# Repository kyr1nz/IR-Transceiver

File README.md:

# IR-Transceiver
ESP32-based infrared transceiver for receiving, decoding, and transmitting IR signals.

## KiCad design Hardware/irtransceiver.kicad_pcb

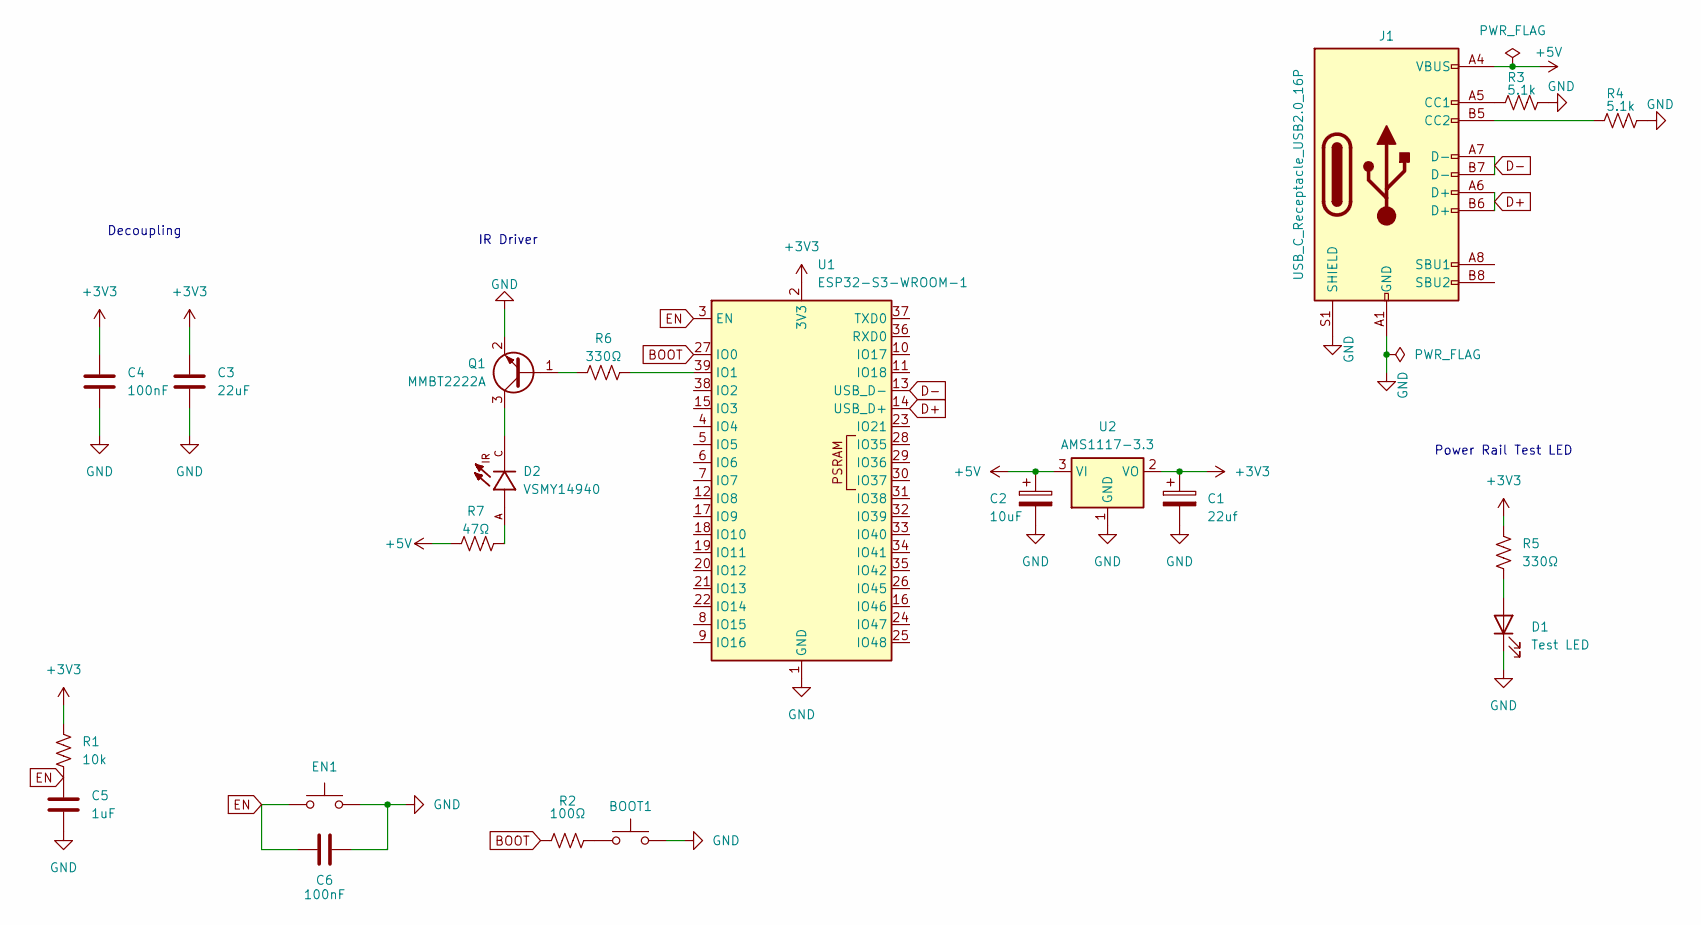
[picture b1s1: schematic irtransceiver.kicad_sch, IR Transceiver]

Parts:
BOOT1: BOOT Switch; SW-SMD_L3.9-W3.0-P4.45; LCSC C720477
C1: 22uf; C_1210_3225Metric; LCSC C696813
C2: 10uF; C_1210_3225Metric; LCSC C7194
C3: 22uF; C_0805_2012Metric; LCSC C602037
C4, C6: 100nF; C_0805_2012Metric; LCSC C83055
C5: 1uF; C_0805_2012Metric; LCSC C28323
D1: Test LED; LED_0603_1608Metric; LCSC C126319
D2: VSMY14940; LED_MY14940_VIS; PARTREV 1.6; LCSC C511069
EN1: EN Switch; SW-SMD_L3.9-W3.0-P4.45; LCSC C720477
J1: USB_C_Receptacle_USB2.0_16P; USB_C_Receptacle_GCT_USB4105-xx-A_16P_TopMnt_Horizontal; LCSC C393939
Q1: MMBT2222A; SOT-23; LCSC C179396
R1: 10k; R_0805_2012Metric; LCSC C2907219
R2: 100Ω; R_0805_2012Metric; LCSC C105577
R3, R4: 5.1k; R_0805_2012Metric; LCSC C27834
R5: 330Ω; R_0805_2012Metric; LCSC C17630
R6: 330Ω; R_0603_1608Metric; LCSC C105879
R7: 47Ω; R_2512_6332Metric; LCSC C175524
U1: ESP32-S3-WROOM-1; LCSC C2913202
U2: AMS1117-3.3; SOT-223-3_TabPin2; LCSC C6186

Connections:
+3V3: C1.1, C3.1, C4.1, R1.1, R5.1, U1.2 (3V3), U2.2 (VO)
+5V: C2.1, J1.A4 (VBUS), J1.A9 (VBUS), J1.B4 (VBUS), J1.B9 (VBUS), R7.1, U2.3 (VI)
BOOT: R2.1, U1.27 (IO0)
D+: J1.A6 (D+), J1.B6 (D+), U1.14 (USB_D+)
D-: J1.A7 (D-), J1.B7 (D-), U1.13 (USB_D-)
EN: C5.1, C6.1, EN1.1, R1.2, U1.3 (EN)
GND: BOOT1.2, C1.2, C2.2, C3.2, C4.2, C5.2, C6.2, D1.1 (K), EN1.2, J1.A1 (GND), J1.A12 (GND), J1.B1 (GND), J1.B12 (GND), J1.S1 (SHIELD), Q1.2 (E), R3.2, R4.2, U1.1 (GND), U1.40 (GND), U1.41 (GND), U2.1 (GND)
unnamed: BOOT1.1, R2.2
unnamed: D1.2 (A), R5.2
unnamed: D2.A, R7.2
unnamed: J1.A5 (CC1), R3.1
unnamed: J1.B5 (CC2), R4.1
unnamed: Q1.1 (B), R6.1
unnamed: D2.C, Q1.3 (C)
unnamed: R6.2, U1.39 (IO1)

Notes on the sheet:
Decoupling
Power Rail Test LED
IR Driver

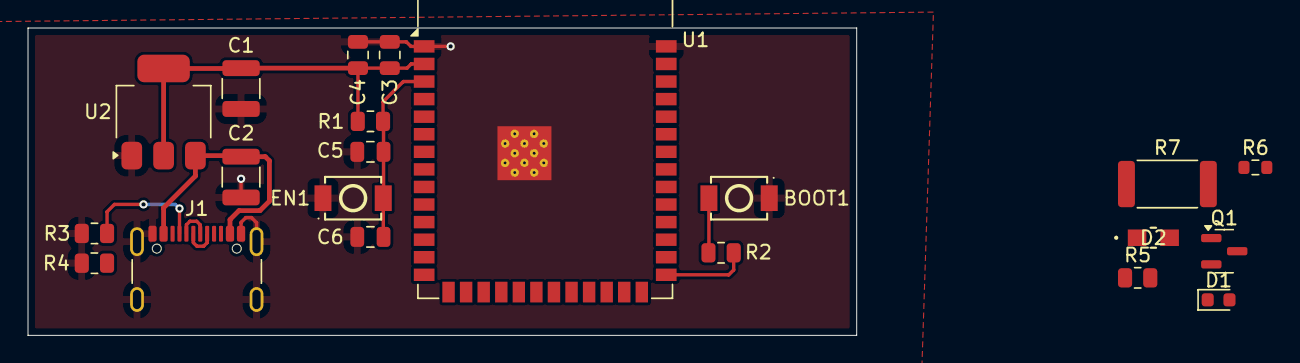
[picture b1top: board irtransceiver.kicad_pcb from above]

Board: 2 copper layers, 59.9 x 22.2 mm, 21 parts (0 on the bottom side), 15 nets.
